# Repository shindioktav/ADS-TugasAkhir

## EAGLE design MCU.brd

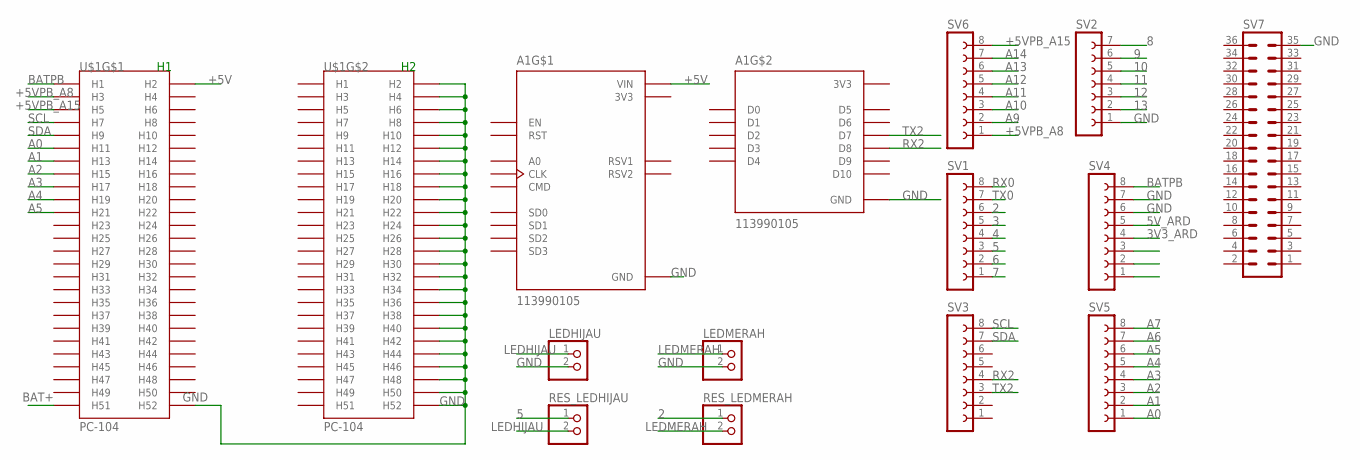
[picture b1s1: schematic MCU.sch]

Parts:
A1: 113990105; SEEED_113990105
LEDHIJAU: PINHD-1X2; 1X02
LEDMERAH: PINHD-1X2; 1X02
RES_LEDHIJAU: PINHD-1X2; 1X02
RES_LEDMERAH: PINHD-1X2; 1X02
SV1, SV3, SV4, SV5, SV6: FE08-1; FE08
SV2: FE07-1; FE07
SV7: MA18-2
U$1: PC-104

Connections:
2: RES_LEDMERAH.1, SV1.6
3: SV1.5
3V3: A1.J1_11 (3V3), A1.J2_6 (3V3), A1.J2_15 (3V3)
3V3_ARD: SV4.4
4: SV1.4
5: RES_LEDHIJAU.1, SV1.3
5V_ARD: SV4.5
6: SV1.2
7: SV1.1
8: SV2.7
9: SV2.6
10: SV2.5
11: SV2.4
12: SV2.3
13: SV2.2
+5V: A1.J1_15 (VIN), U$1.P$2 (H2)
+5VPB_A8: SV6.1, U$1.P$3 (H3)
+5VPB_A15: SV6.8, U$1.P$5 (H5)
A0: SV5.1, U$1.P$11 (H11)
A1: SV5.2, U$1.P$13 (H13)
A2: SV5.3, U$1.P$15 (H15)
A3: SV5.4, U$1.P$17 (H17)
A4: SV5.5, U$1.P$19 (H19)
A5: SV5.6, U$1.P$21 (H21)
A6: SV5.7
A7: SV5.8
A9: SV6.2
A10: SV6.3
A11: SV6.4
A12: SV6.5
A13: SV6.6
A14: SV6.7
BAT+: U$1.P$51 (H51)
BATPB: SV4.8, U$1.P$1 (H1)
GND: A1.J1_10 (GND), A1.J1_14 (GND), A1.J2_7 (GND), A1.J2_14 (GND), LEDHIJAU.2, LEDMERAH.2, SV2.1, SV4.6, SV4.7, SV7.35, U$1.P$52 (H52), U$1.P$54 (H2), U$1.P$56 (H4), U$1.P$58 (H6), U$1.P$60 (H8), U$1.P$62 (H10), U$1.P$64 (H12), U$1.P$66 (H14), U$1.P$68 (H16), U$1.P$70 (H18), U$1.P$72 (H20), U$1.P$74 (H22), U$1.P$76 (H24), U$1.P$78 (H26), U$1.P$80 (H28), U$1.P$82 (H30), U$1.P$84 (H32), U$1.P$86 (H34), U$1.P$88 (H36), U$1.P$90 (H38), U$1.P$92 (H40), U$1.P$94 (H42), U$1.P$96 (H44), U$1.P$98 (H46), U$1.P$100 (H48), U$1.P$102 (H50), U$1.P$104 (H52)
LEDHIJAU: LEDHIJAU.1, RES_LEDHIJAU.2
LEDMERAH: LEDMERAH.1, RES_LEDMERAH.2
RX0: SV1.8
RX2: A1.J2_11 (D8), SV3.4
SCL: SV3.8, U$1.P$7 (H7)
SDA: SV3.7, U$1.P$9 (H9)
TX0: SV1.7
TX2: A1.J2_10 (D7), SV3.3

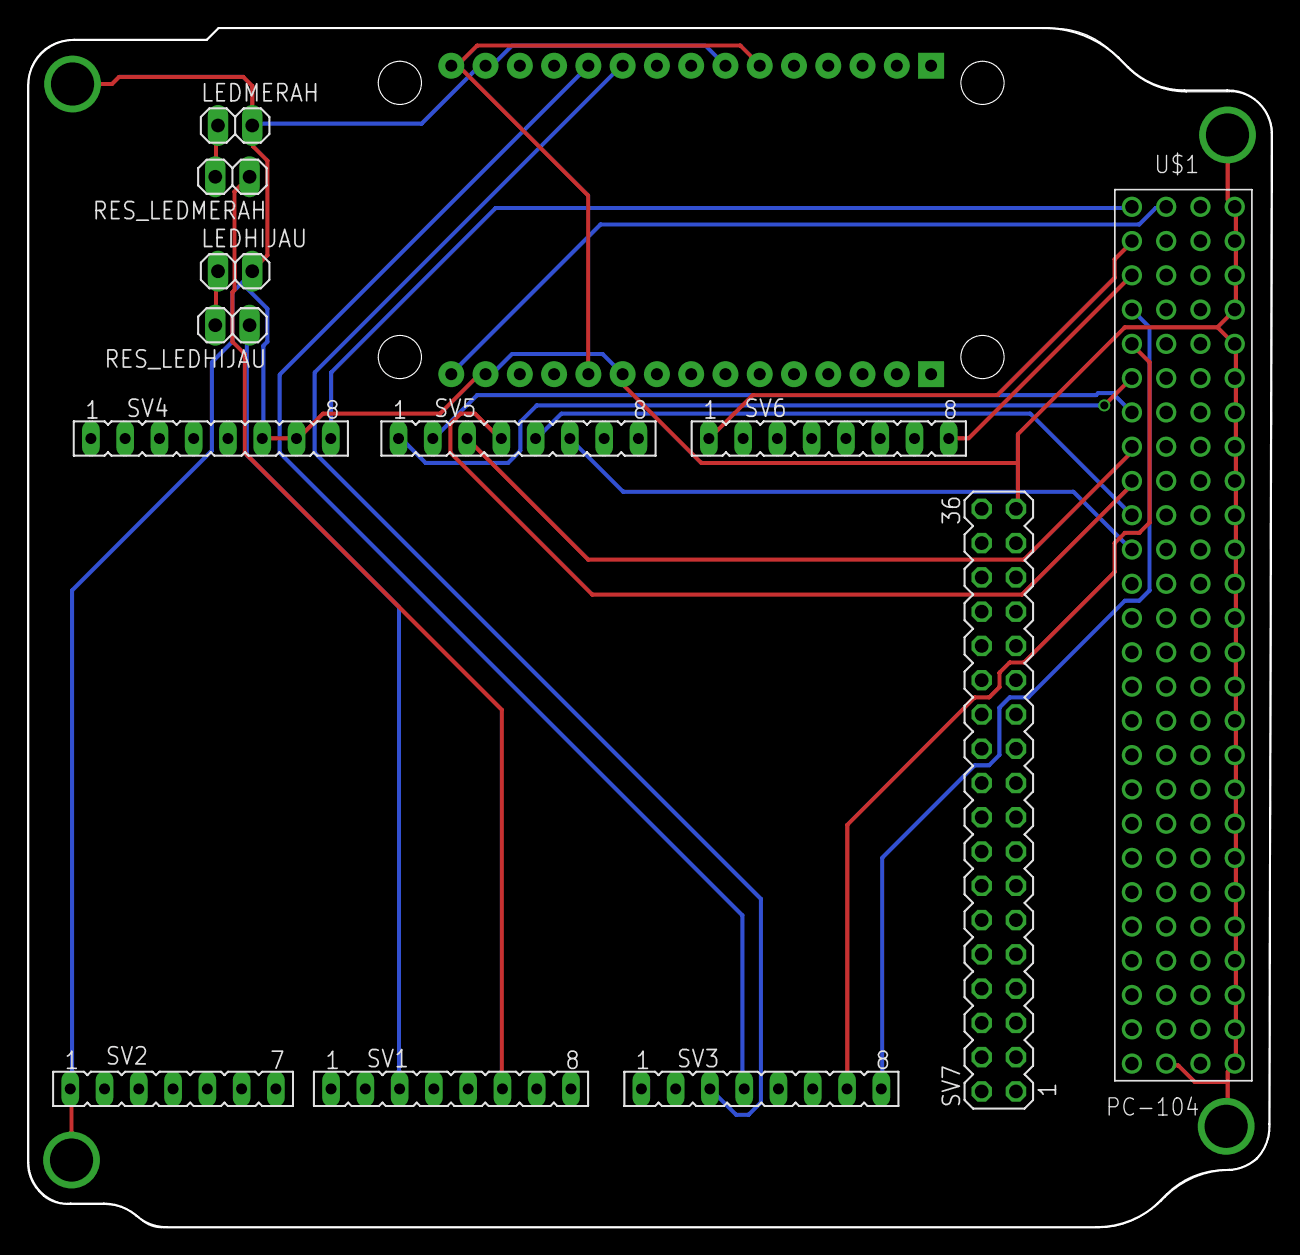
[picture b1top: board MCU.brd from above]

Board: 2 copper layers, 92.2 x 88.9 mm, 13 parts (1 on the bottom side), 20 nets.

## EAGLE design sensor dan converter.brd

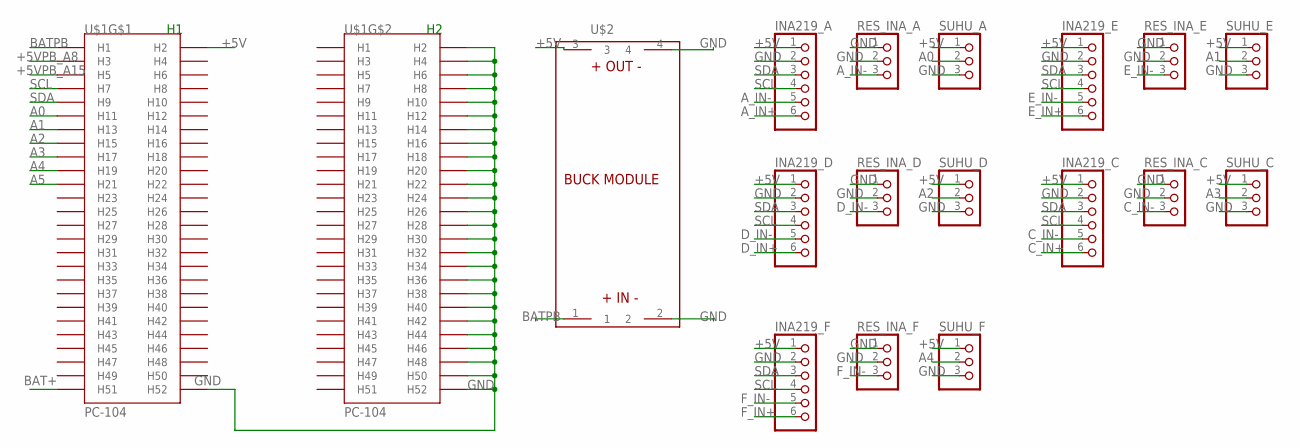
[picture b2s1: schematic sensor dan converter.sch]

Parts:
INA219_A, INA219_C, INA219_D, INA219_E, INA219_F: PINHD-1X6; 1X06
RES_INA_A: PINHD-1X3; 1X03
RES_INA_C: PINHD-1X3; 1X03
RES_INA_D: PINHD-1X3; 1X03
RES_INA_E: PINHD-1X3; 1X03
RES_INA_F: PINHD-1X3; 1X03
SUHU_A: PINHD-1X3; 1X03
SUHU_C: PINHD-1X3; 1X03
SUHU_D: PINHD-1X3; 1X03
SUHU_E: PINHD-1X3; 1X03
SUHU_F: PINHD-1X3; 1X03
U$1: PC-104
U$2: BUCK_MODULEWITH_SMDPADS&THROUGHHOLES; BUCK_MODULE

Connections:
+5V: INA219_A.1, INA219_C.1, INA219_D.1, INA219_E.1, INA219_F.1, SUHU_A.1, SUHU_C.1, SUHU_D.1, SUHU_E.1, SUHU_F.1, U$1.P$2 (H2), U$2.3
+5VPB_A8: U$1.P$3 (H3)
+5VPB_A15: U$1.P$5 (H5)
A0: SUHU_A.2, U$1.P$11 (H11)
A1: SUHU_E.2, U$1.P$13 (H13)
A2: SUHU_D.2, U$1.P$15 (H15)
A3: SUHU_C.2, U$1.P$17 (H17)
A4: SUHU_F.2, U$1.P$19 (H19)
A5: U$1.P$21 (H21)
A_IN+: INA219_A.6
A_IN-: INA219_A.5, RES_INA_A.3
BAT+: U$1.P$51 (H51)
BATPB: U$1.P$1 (H1), U$2.1
C_IN+: INA219_C.6
C_IN-: INA219_C.5, RES_INA_C.3
D_IN+: INA219_D.6
D_IN-: INA219_D.5, RES_INA_D.3
E_IN+: INA219_E.6
E_IN-: INA219_E.5, RES_INA_E.3
F_IN+: INA219_F.6
F_IN-: INA219_F.5, RES_INA_F.3
GND: INA219_A.2, INA219_C.2, INA219_D.2, INA219_E.2, INA219_F.2, RES_INA_A.1, RES_INA_A.2, RES_INA_C.1, RES_INA_C.2, RES_INA_D.1, RES_INA_D.2, RES_INA_E.1, RES_INA_E.2, RES_INA_F.1, RES_INA_F.2, SUHU_A.3, SUHU_C.3, SUHU_D.3, SUHU_E.3, SUHU_F.3, U$1.P$52 (H52), U$1.P$54 (H2), U$1.P$56 (H4), U$1.P$58 (H6), U$1.P$60 (H8), U$1.P$62 (H10), U$1.P$64 (H12), U$1.P$66 (H14), U$1.P$68 (H16), U$1.P$70 (H18), U$1.P$72 (H20), U$1.P$74 (H22), U$1.P$76 (H24), U$1.P$78 (H26), U$1.P$80 (H28), U$1.P$82 (H30), U$1.P$84 (H32), U$1.P$86 (H34), U$1.P$88 (H36), U$1.P$90 (H38), U$1.P$92 (H40), U$1.P$94 (H42), U$1.P$96 (H44), U$1.P$98 (H46), U$1.P$100 (H48), U$1.P$102 (H50), U$1.P$104 (H52), U$2.2, U$2.4
SCL: INA219_A.4, INA219_C.4, INA219_D.4, INA219_E.4, INA219_F.4, U$1.P$7 (H7)
SDA: INA219_A.3, INA219_C.3, INA219_D.3, INA219_E.3, INA219_F.3, U$1.P$9 (H9)

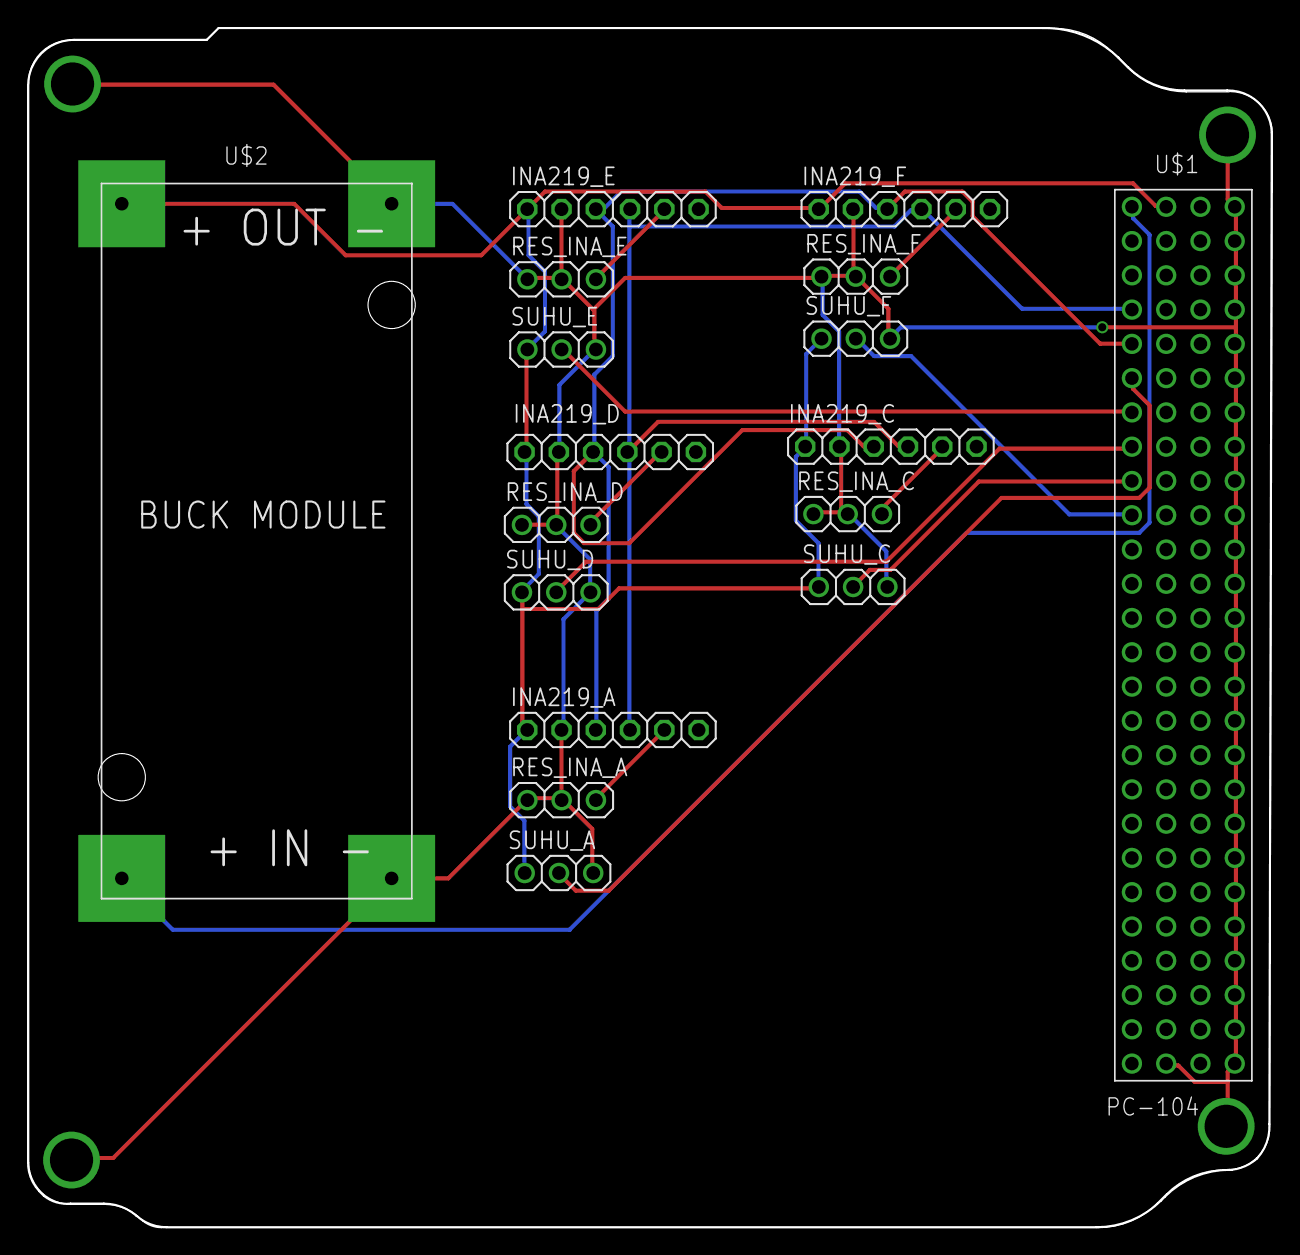
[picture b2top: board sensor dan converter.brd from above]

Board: 2 copper layers, 92.2 x 88.9 mm, 17 parts (0 on the bottom side), 15 nets.

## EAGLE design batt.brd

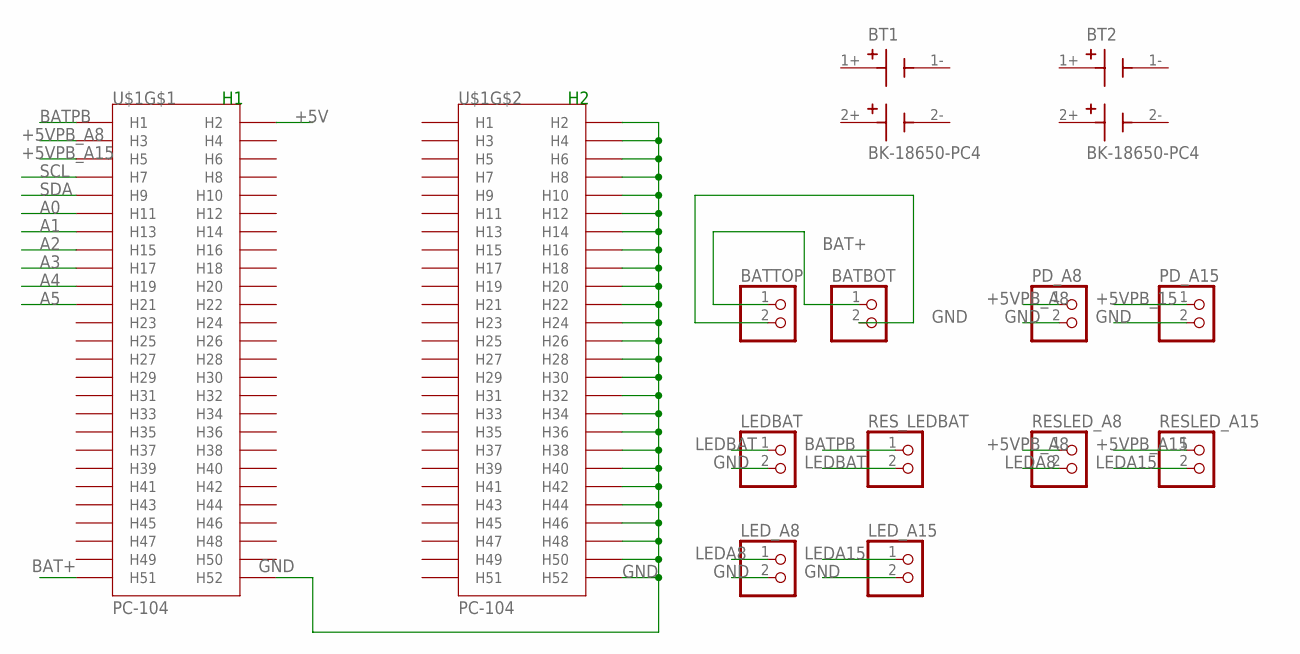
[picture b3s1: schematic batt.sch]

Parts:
BATBOT: PINHD-1X2; 1X02
BATTOP: PINHD-1X2; 1X02
BT1, BT2: BK-18650-PC4; BAT_BK-18650-PC4
LEDBAT: PINHD-1X2; 1X02
LED_A8, LED_A15: PINHD-1X2; 1X02
PD_A8, PD_A15: PINHD-1X2; 1X02
RESLED_A8, RESLED_A15: PINHD-1X2; 1X02
RES_LEDBAT: PINHD-1X2; 1X02
U$1: PC-104

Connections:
+5V: U$1.P$2 (H2)
+5VPB_15: PD_A15.1
+5VPB_A8: PD_A8.1, RESLED_A8.1, U$1.P$3 (H3)
+5VPB_A15: RESLED_A15.1, U$1.P$5 (H5)
A0: U$1.P$11 (H11)
A1: U$1.P$13 (H13)
A2: U$1.P$15 (H15)
A3: U$1.P$17 (H17)
A4: U$1.P$19 (H19)
A5: U$1.P$21 (H21)
BAT+: BATBOT.1, BATTOP.1, U$1.P$51 (H51)
BATPB: RES_LEDBAT.1, U$1.P$1 (H1)
GND: BATBOT.2, BATTOP.2, LEDBAT.2, LED_A8.2, LED_A15.2, PD_A8.2, PD_A15.2, U$1.P$52 (H52), U$1.P$54 (H2), U$1.P$56 (H4), U$1.P$58 (H6), U$1.P$60 (H8), U$1.P$62 (H10), U$1.P$64 (H12), U$1.P$66 (H14), U$1.P$68 (H16), U$1.P$70 (H18), U$1.P$72 (H20), U$1.P$74 (H22), U$1.P$76 (H24), U$1.P$78 (H26), U$1.P$80 (H28), U$1.P$82 (H30), U$1.P$84 (H32), U$1.P$86 (H34), U$1.P$88 (H36), U$1.P$90 (H38), U$1.P$92 (H40), U$1.P$94 (H42), U$1.P$96 (H44), U$1.P$98 (H46), U$1.P$100 (H48), U$1.P$102 (H50), U$1.P$104 (H52)
LEDA8: LED_A8.1, RESLED_A8.2
LEDA15: LED_A15.1, RESLED_A15.2
LEDBAT: LEDBAT.1, RES_LEDBAT.2
SCL: U$1.P$7 (H7)
SDA: U$1.P$9 (H9)

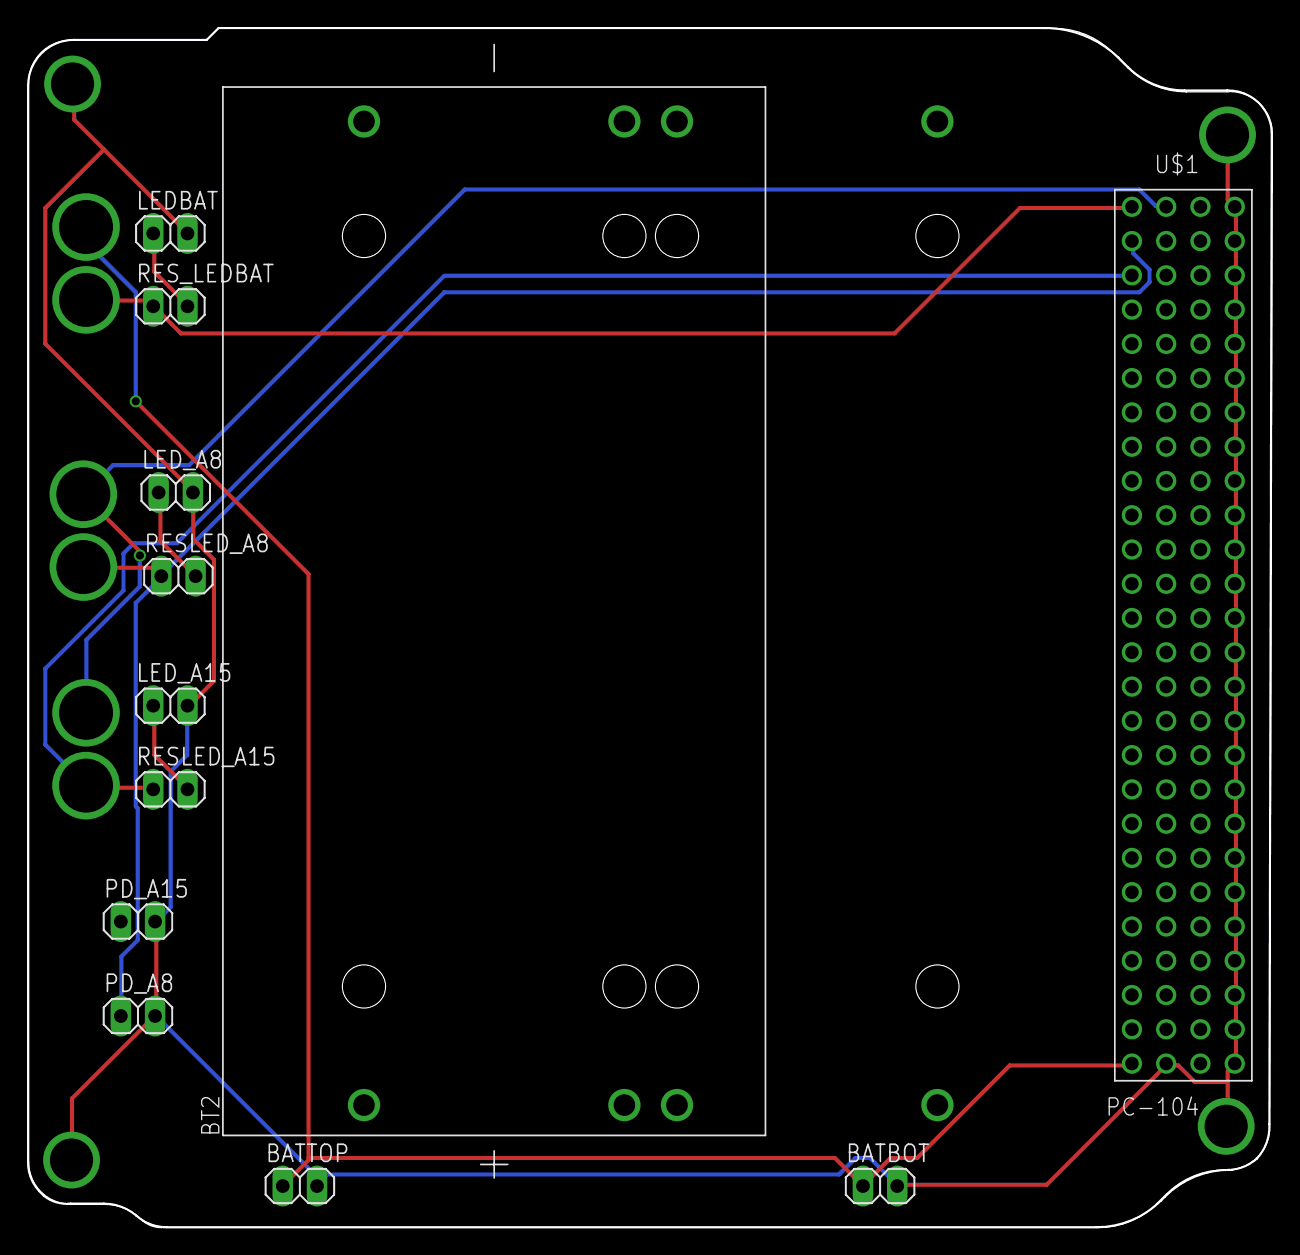
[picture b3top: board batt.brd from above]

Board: 2 copper layers, 92.2 x 88.9 mm, 13 parts (1 on the bottom side), 8 nets.

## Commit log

2022-09-05 Rename 1_sumbu_arduino_revisi_7.0.ino to Code_Arduino
2022-09-05 Rename UART_ESP_FLOAT_THINGSPEAK_v4.ino to Code_NodeMCU
2022-09-05 Rename code_baru.m to Simulasi_MatLab
